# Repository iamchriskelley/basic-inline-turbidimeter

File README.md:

#Basic Inline Turbidimeter
##Purpose  
The Basic Inline Turbidimeter is designed to measure turbidity in a body of water, automatically, for the lowest possible price.  

##Function  
_How does the device measure a parameter?_  
This device is a back-scatter [nephelometrer](https://en.wikipedia.org/wiki/Nephelometer). A pair of infrared light-emitting diodes (IR LED) are mounted on either side of a light-to-frequency sensor. Some portion of this emitted light is scattered by suspended sediment as it passes through a sample of water. This scattered light is detected by an IR-sensitive [photodiode](https://en.wikipedia.org/wiki/Photodiode) mounted at a right angle to the center of the IR LED's light beam. The intensity of light detected by the photodiode is referenced to a calibration curve stored in the device's memory to interpolate the corresponding turbidity value, measured in [nephelometric turbidity units (NTU)](http://or.water.usgs.gov/grapher/fnu.html).  

_How does the device record data?_  
This device contains an SD card slot for storing data.   

_How does the device display data?_  
This device is intended for standalone data logging and does not include a display.  

_What units does the device report in?_  
Like all AWQUA turbidimeters, this device reports readings in  [nephelometric turbidity units (NTU)](http://or.water.usgs.gov/grapher/fnu.html).  

_How does the device communicate data electronically?_  
This device does not possess data telemetry capabilities, however they may be added for additional cost. See the [Communications](https://github.com/AWQUA/Communication) repo for options. 

##Use Case  
_Where can the device be safely used?_  
This device can handle temperatures up to 70C, and is intended for field conditions. It is water proof to at least one foot.

##Power  
_How is the device powered?_  
This device uses 3.3V DC power, and requires less than 100mA of current, and uses an internal 3.7V lithium polymer battery.

_How much power does it use?_  
In automated testing, this device was capable of taking a measurement every 15 minutes for 29.5 days.

##Standard and Testing  
_How was the device tested?_  
This device has so far only been tested in the Open Source Water lab. The testing consisted of:
(1) immersing a prototype device in a water bath which contains a spin plate for bath mixing  
(2) adding small doses of a colloidal suspension to the water bath while relaying readings from the prototype via Bluetooth  every 10 seconds
(3) on every fourth dose of colloidal suspension, sampling the water bath with a commercial handheld turbidimeter  
(4) analyzing the fit between the commercial and prototype open-source turbidimeter

_How did it perform?_  
Test results may be found in the `testing` subdirectory in the file `basic-inline-turbidimeter_analysis.20151021.xlsx`. These data will be updated as further testing is conducted.

_What performance standards does the device meet?_  
We have not evaluated this device against existing standards for backscatter turbidimeters yet, nor have we yet developed a new standard.

##Construction  

###Bill of Materials
| Quantity  | Part Description | Example Price (each) |
| :-------------: | ------------- | :-------------: |
| 1 | ATMega328P-PU microprocessor  | [$2.90](http://www.electrodragon.com/product/atmega328-with-arduino-optiboot-uno/)|
| 1 | LMT86 temperature sensor  | [$1.00](http://www.mouser.com/ProductDetail/Texas-Instruments/LMT86LP/?qs=sGAEpiMZZMvfFCidbTccA1jyVRrxk5nB%252bTEjPRynSGM%3d)|
| 1 | TSL230BRD  | [$5.03](http://www.mouser.com/ProductDetail/ams/TSL230BRD-TR/?qs=sGAEpiMZZMu97qiQi8P%252buifvOPr%252b402N67DKHn09PFo%3d)|
| 1 | LP2985 3.3V Voltage regulator  | [$1.04](http://www.mouser.com/ProductDetail/Texas-Instruments/LP2985-33DBVT/?qs=paYhMW8qfivCywxvLCGbYQ%3D%3D)|
| 2 | 10uF aluminum electrolytic capacitors  | [$0.24](http://www.mouser.com/ProductDetail/Nichicon/ULD1J100MDD1TD/?qs=sGAEpiMZZMvwFf0viD3Y3c1N%2fF%2fpDmX12XlNW9X9Y3vZmYyMo5GpOw%3d%3d)|
| 2 | 22pF ceramic capacitors  | [$0.03](http://www.mouser.com/ProductDetail/Vishay-BC-Components/K220J10C0GF5UH5/?qs=sGAEpiMZZMsh%252b1woXyUXj9nJp%252b8gphztXIKBUu3gv%252bs%3d)|
| 5 | 100nF ceramic capacitors  | [$0.06](http://www.mouser.com/ProductDetail/Vishay-BC-Components/K104Z15Y5VE5TL2/?qs=sGAEpiMZZMsh%252b1woXyUXj5VNmf0jXPWIrWjnp1zAXac%3d)|
| 4 | 100 ohm resistors  | [$0.10](http://www.mouser.com/ProductDetail/KOA-Speer/MOS1-2CT52R101J/?qs=sGAEpiMZZMtlubZbdhIBICYVxaT5CDYBpEIIN%2f0BoAk%3d)|
| 1 | 220 ohm resistors  | [$0.10](http://www.mouser.com/ProductDetail/KOA-Speer/MOS1-2CT52R221J/?qs=sGAEpiMZZMtlubZbdhIBICYVxaT5CDYBStqm8FrIljg%3d)|
| 1 | 1K ohm resistors 1% tolerance | [$0.10](http://www.mouser.com/ProductDetail/Vishay-Beyschlag/MBB02070C1001FCT00/?qs=sGAEpiMZZMtlubZbdhIBIAA6NYEPHyksoxlYyK2s%252btM%3d)|
| 4 | 10K ohm resistors  | [$0.10](http://www.mouser.com/ProductDetail/Vishay-Beyschlag/MBA02040C1002FCT00/?qs=sGAEpiMZZMtlubZbdhIBIP7908E9uONJr6Tgqqo7oLA%3d)|
| 1 | IR LED  | [$0.47](http://www.mouser.com/ProductDetail/Kingbright/WP7113SF4C/?qs=sGAEpiMZZMvAL21a%2fDhxMro1KOf4QOs%252bCw5JRgjZK8o%3d)|
| 1 | Momentary contact button  | [$1.50](http://www.mouser.com/)|
| 1 | SPST power switch  | [$1.50](http://www.mouser.com/)|
| x | Header pins (0.1" spacing)  | [$1.50](http://www.mouser.com/)|
|||
||Total Cost:|$xx.xx|
###Circuit Board
####Schematic

####Layout

###Assembly
[forthcoming]  
##FAQ and Troubleshooting  
###Online Resources

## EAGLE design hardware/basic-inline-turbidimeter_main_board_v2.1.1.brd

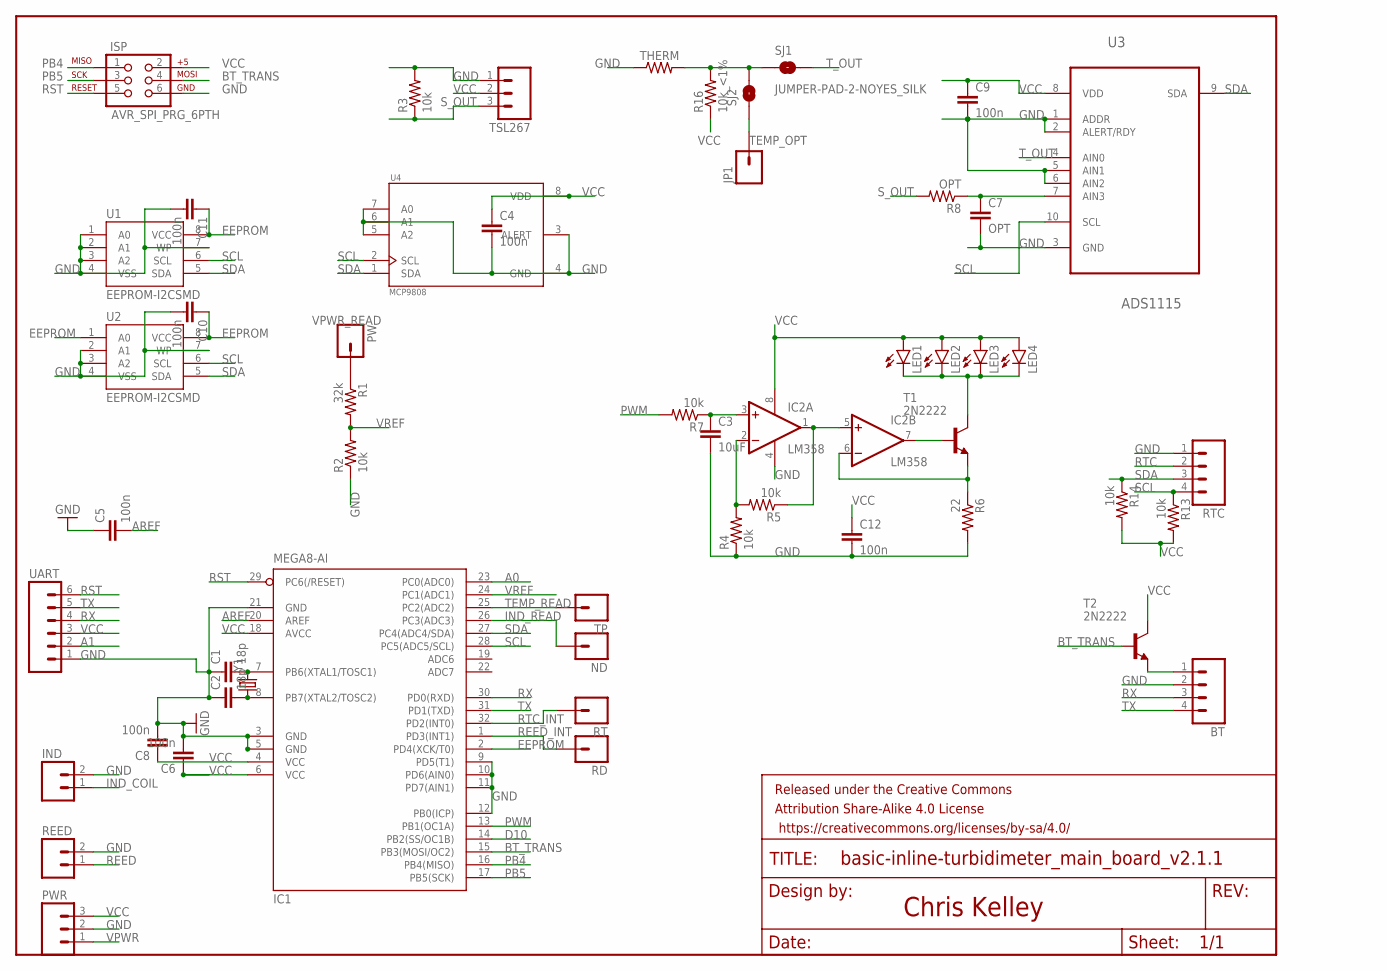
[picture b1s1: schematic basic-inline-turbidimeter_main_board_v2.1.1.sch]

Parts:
BT: M04PTH; 1X04
C1, C2: 18p; 0603-CAP
C3: 10uF; 0603-CAP
C4, C5, C6, C8, C9, C10, C11, C12: 100n; 0603-CAP
C7: OPT; 0603-CAP
FRAME1: FRAME-LETTER; CREATIVE_COMMONS
IC1: MEGA8-AI; TQFP32-08
IC2: LM358; SO08
IND: M02PTH; 1X02
ISP: AVR_SPI_PRG_6PTH; 2X3
JP1: M01PTH; 1X01
LED1, LED2, LED3, LED4: LED5MM
ND: M01PTH; 1X01
PW: M01PTH; 1X01
PWR: M03PTH; 1X03
R1: 32k; 0603-RES
R2, R3, R4, R5, R7, R13, R14: 10k; 0603-RES
R6: 22; 0603-RES
R8: OPT; 0603-RES
R16: 10k_<1%; 0603-RES
RD: M01PTH; 1X01
REED: M02PTH; 1X02
RT: M01PTH; 1X01
RTC: M04PTH; 1X04
SJ1, SJ2: JUMPER-PAD-2-NOYES_SILK; PAD-JUMPER-2-NO_YES_SILK
T1, T2: 2N2222; TO92-EBC-OVAL
THERM: RESISTOR0603-RES; 0603-RES
TP: M01PTH; 1X01
TSL267: M03PTH; 1X03
U1, U2: EEPROM-I2CSMD; SO08
U3: ADS1115; SOP50P490X110-10N
U4: MCP9808; SOP65P490X110-8N
UART: M06SILK_FEMALE_PTH; 1X06
Y1: CRYSTAL5X3; CRYSTAL-SMD-5X3

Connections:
A0: IC1.23 (PC0(ADC0))
A1: UART.2
AREF: C5.2, IC1.20 (AREF)
BT_TRANS: IC1.15 (PB3(MOSI/OC2)), ISP.4, T2.B
D10: IC1.14 (PB2(SS/OC1B))
EEPROM: C10.1, C11.1, IC1.2 (PD4(XCK/T0)), U1.8 (VCC), U2.1 (A0), U2.8 (VCC)
GND: BT.2, C1.1, C2.1, C3.2, C4.2, C5.1, C6.2, C7.2, C8.2, C9.2, C10.2, C11.2, C12.2, IC1.3 (GND), IC1.5 (GND), IC1.9 (PD5(T1)), IC1.10 (PD6(AIN0)), IC1.11 (PD7(AIN1)), IC1.12 (PB0(ICP)), IC1.21 (GND), IC2.4 (V-), IND.2, ISP.6, PWR.2, R2.1, R3.2, R4.1, R6.2, REED.2, RTC.1, THERM.1, TSL267.1, U1.1 (A0), U1.2 (A1), U1.3 (A2), U1.4 (VSS), U1.7 (WP), U2.2 (A1), U2.3 (A2), U2.4 (VSS), U2.7 (WP), U3.1 (ADDR), U3.2 (ALERT/RDY), U3.3 (GND), U3.5 (AIN1), U3.6 (AIN2), U4.3 (ALERT), U4.4 (GND), U4.5 (A2), U4.6 (A1), U4.7 (A0), UART.1
IND_COIL: IND.1
IND_READ: IC1.26 (PC3(ADC3)), ND.1
unnamed: LED1.K (C), LED2.K (C), LED3.K (C), LED4.K (C), T1.C
unnamed: C7.1, R8.1, U3.7 (AIN3)
unnamed: C3.1, IC2.3 (+IN), R7.1
unnamed: IC2.1 (OUT), IC2.5 (+IN), R5.1
unnamed: IC2.7 (OUT), T1.B
unnamed: IC2.2 (-IN), R4.2, R5.2
unnamed: IC2.6 (-IN), R6.1, T1.E
unnamed: BT.1, T2.E
unnamed: R16.2, SJ1.1, SJ2.2, THERM.2
PB4: IC1.16 (PB4(MISO)), ISP.1
PB5: IC1.17 (PB5(SCK)), ISP.3
PWM: IC1.13 (PB1(OC1A)), R7.2
Q1: C2.2, IC1.8 (PB7(XTAL2/TOSC2)), Y1.1
Q2: C1.2, IC1.7 (PB6(XTAL1/TOSC1)), Y1.3 (2)
REED: REED.1
REED_INT: IC1.1 (PD3(INT1)), RD.1
RST: IC1.29 (PC6(/RESET)), ISP.5, UART.6
RTC: RTC.2
RTC_INT: IC1.32 (PD2(INT0)), RT.1
RX: BT.3, IC1.30 (PD0(RXD)), UART.4
SCL: IC1.28 (PC5(ADC5/SCL)), R13.1, RTC.4, U1.6 (SCL), U2.6 (SCL), U3.10 (SCL), U4.2 (SCL)
SDA: IC1.27 (PC4(ADC4/SDA)), R14.1, RTC.3, U1.5 (SDA), U2.5 (SDA), U3.9 (SDA), U4.1 (SDA)
S_OUT: R3.1, R8.2, TSL267.3
TEMP_OPT: JP1.1, SJ2.1
TEMP_READ: IC1.25 (PC2(ADC2)), TP.1
TX: BT.4, IC1.31 (PD1(TXD)), UART.5
T_OUT: SJ1.2, U3.4 (AIN0)
VCC: C4.1, C6.1, C8.1, C9.1, C12.1, IC1.4 (VCC), IC1.6 (VCC), IC1.18 (AVCC), IC2.8 (V+), ISP.2, LED1.A, LED2.A, LED3.A, LED4.A, PWR.3, R13.2, R14.2, R16.1, T2.C, TSL267.2, U3.8 (VDD), U4.8 (VDD), UART.3
VPWR: PWR.1
VPWR_READ: PW.1, R1.1
VREF: IC1.24 (PC1(ADC1)), R1.2, R2.2

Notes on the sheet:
Chris Kelley

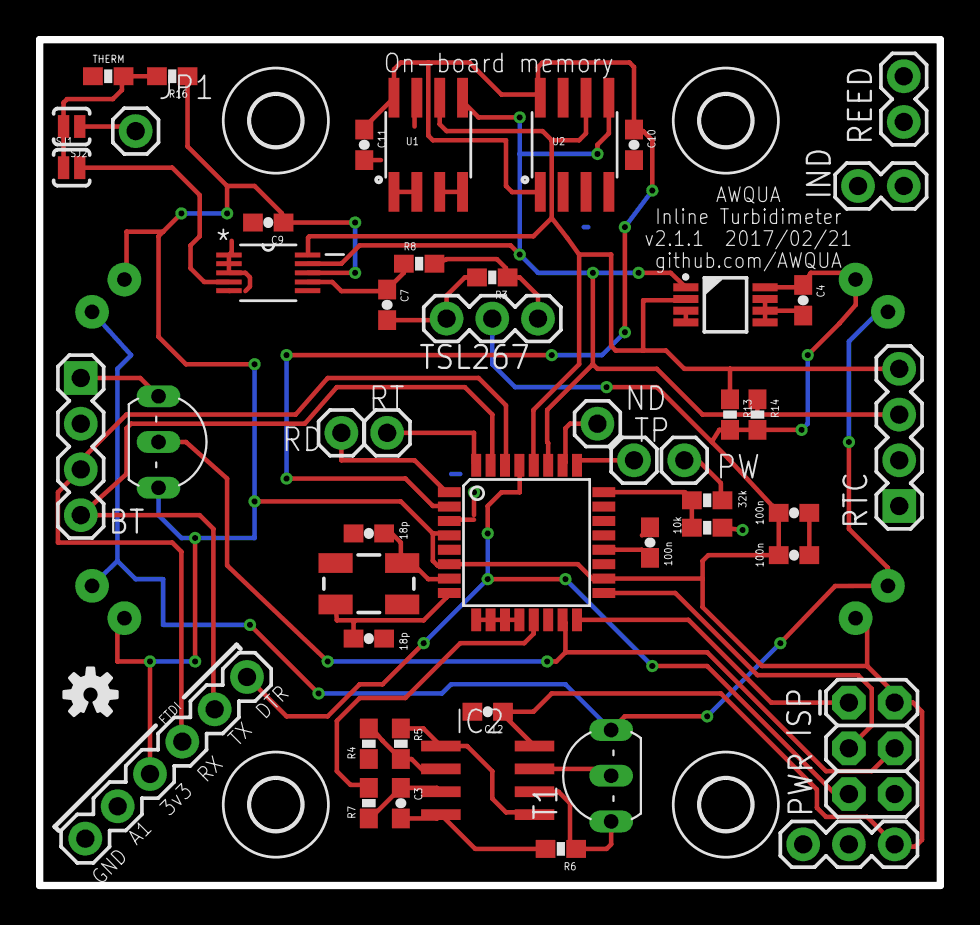
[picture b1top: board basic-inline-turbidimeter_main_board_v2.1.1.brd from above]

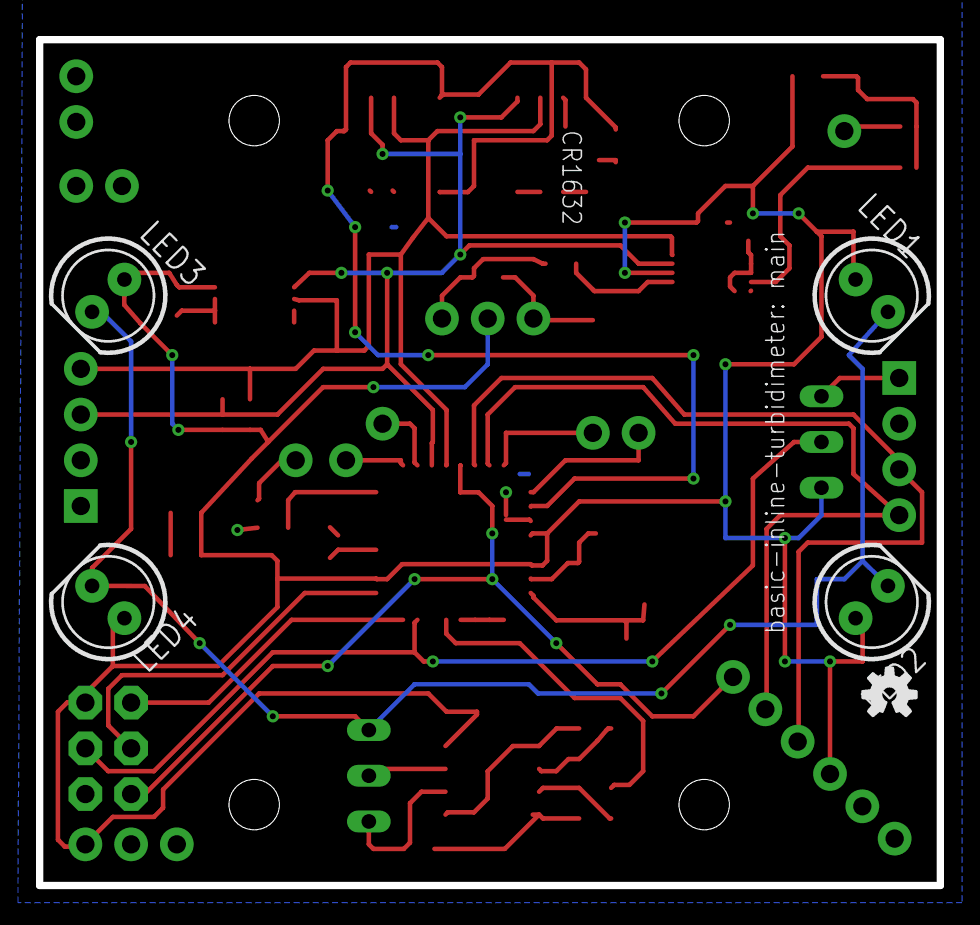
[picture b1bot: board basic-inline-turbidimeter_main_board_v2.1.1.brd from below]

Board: 2 copper layers, 50.0 x 47.0 mm, 60 parts (5 on the bottom side), 33 nets.

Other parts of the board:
U$1, U$3, U$5, U$6: 2,8
U$2, U$8: OSHW-LOGO-S

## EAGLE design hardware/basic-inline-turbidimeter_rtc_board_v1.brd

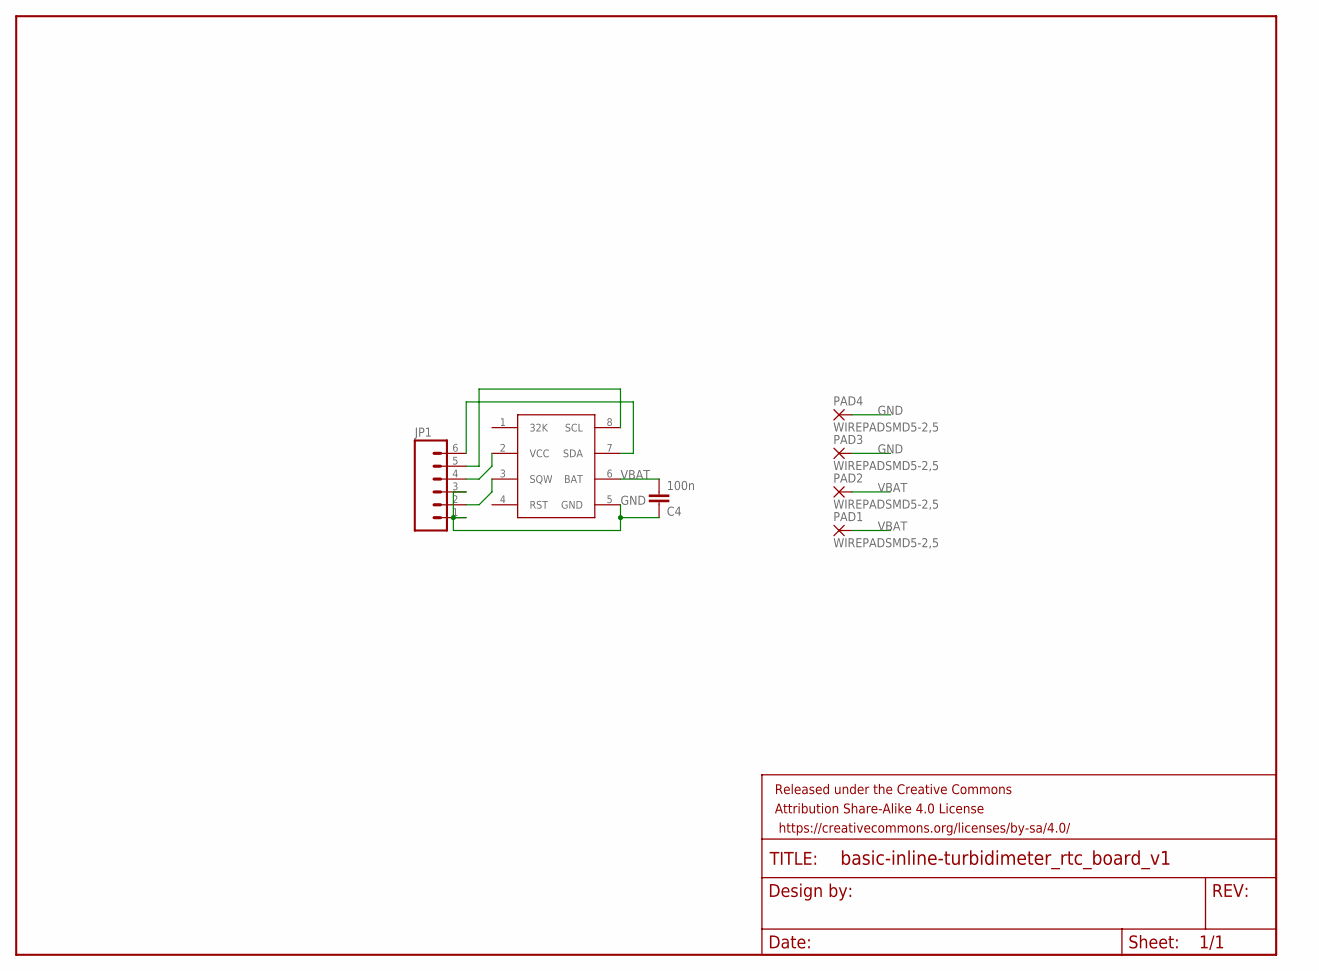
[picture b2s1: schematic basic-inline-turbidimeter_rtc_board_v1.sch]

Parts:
*RTC: DS3231M
C4: 100n; 0603-CAP
FRAME1: FRAME-LETTER; CREATIVE_COMMONS
JP1: M06SILK_FEMALE_PTH; 1X06
PAD1, PAD2, PAD3, PAD4: WIREPADSMD5-2,5; 5-2,5

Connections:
GND: *RTC.5 (GND), C4.1, JP1.1, JP1.3, PAD3.1, PAD4.1
unnamed: *RTC.3 (SQW), JP1.2
SCL: *RTC.8 (SCL), JP1.5
SDA: *RTC.7 (SDA), JP1.6
VBAT: *RTC.6 (BAT), C4.2, PAD1.1, PAD2.1
VCC: *RTC.2 (VCC), JP1.4

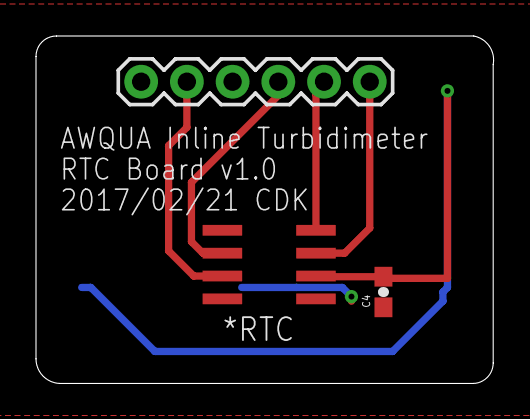
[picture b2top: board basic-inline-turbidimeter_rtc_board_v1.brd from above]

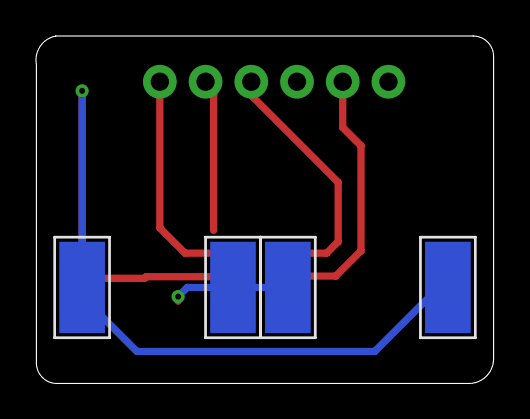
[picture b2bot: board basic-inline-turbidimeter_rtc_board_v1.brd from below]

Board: 2 copper layers, 25.4 x 19.3 mm, 8 parts (4 on the bottom side), 6 nets.

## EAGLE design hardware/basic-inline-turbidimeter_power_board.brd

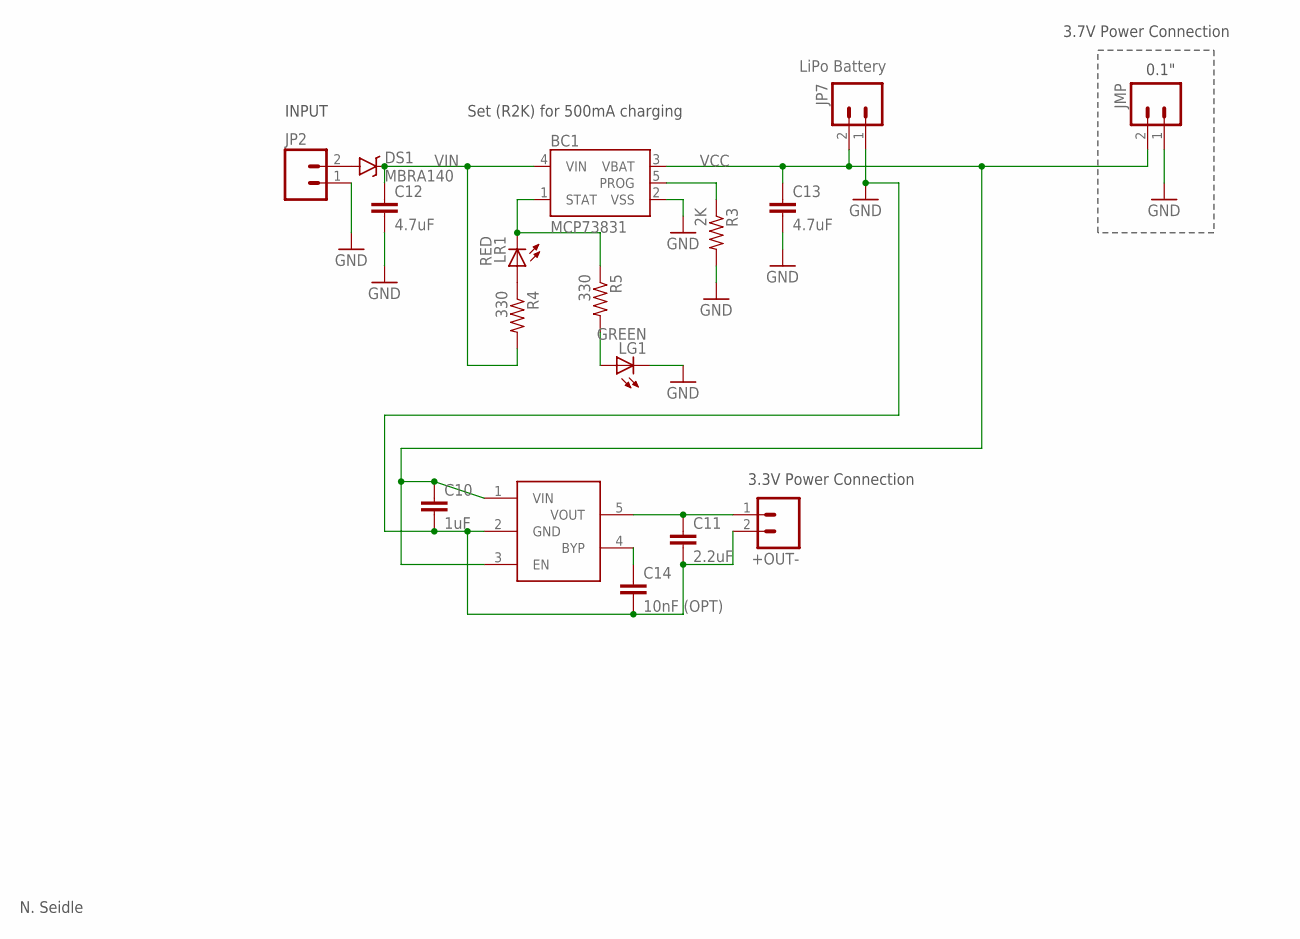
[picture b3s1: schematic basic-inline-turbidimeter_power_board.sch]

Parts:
+OUT-: M02PTH; 1X02
BC1: MCP73831; SOT23-5
C10: 1uF; 0603-CAP
C11: 2.2uF; 0603-CAP
C12, C13: 4.7uF; 0402-CAP
C14: 10nF (OPT); 0603-CAP
DS1: MBRA140; SMA-DIODE
JMP: M02PTH; 1X02
JP2: M02PTH; 1X02
JP7: LiPo Battery; JST-2-SMD
LG1: GREEN; LED-0603
LR1: RED; LED-0603
R3: 2K; 0402-RES
R4, R5: 330; 0402-RES
VR1: LP2985

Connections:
GND: +OUT-.2, BC1.2 (VSS), C10.2, C11.2, C12.2, C13.2, C14.2, JMP.1, JP2.1, JP7.1, LG1.C, R3.2, VR1.2 (GND)
unnamed: C14.1, VR1.4 (BYP)
unnamed: LG1.A, R5.2
unnamed: LR1.A, R4.1
unnamed: +OUT-.1, C11.1, VR1.5 (VOUT)
unnamed: DS1.A, JP2.2
PROG: BC1.5 (PROG), R3.1
STAT: BC1.1 (STAT), LR1.C, R5.1
VCC: BC1.3 (VBAT), C10.1, C13.1, JMP.2, JP7.2, VR1.1 (VIN), VR1.3 (EN)
VIN: BC1.4 (VIN), C12.1, DS1.C, R4.2

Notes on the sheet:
3.7V Power Connection
0.1"
N. Seidle
3.3V Power Connection
Set (R2K) for 500mA charging
INPUT

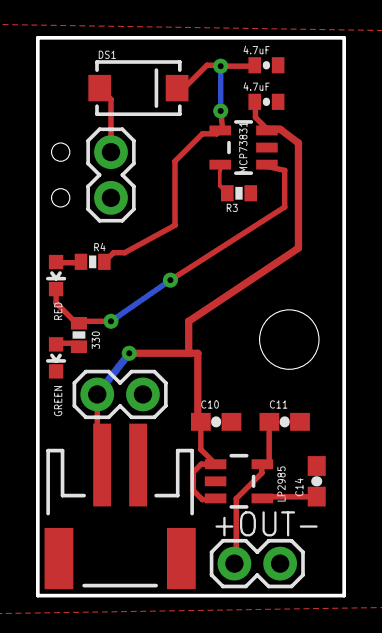
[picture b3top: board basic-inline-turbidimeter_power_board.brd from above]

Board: 2 copper layers, 17.0 x 31.0 mm, 18 parts (0 on the bottom side), 10 nets.

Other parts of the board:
JP1: STAND-OFF

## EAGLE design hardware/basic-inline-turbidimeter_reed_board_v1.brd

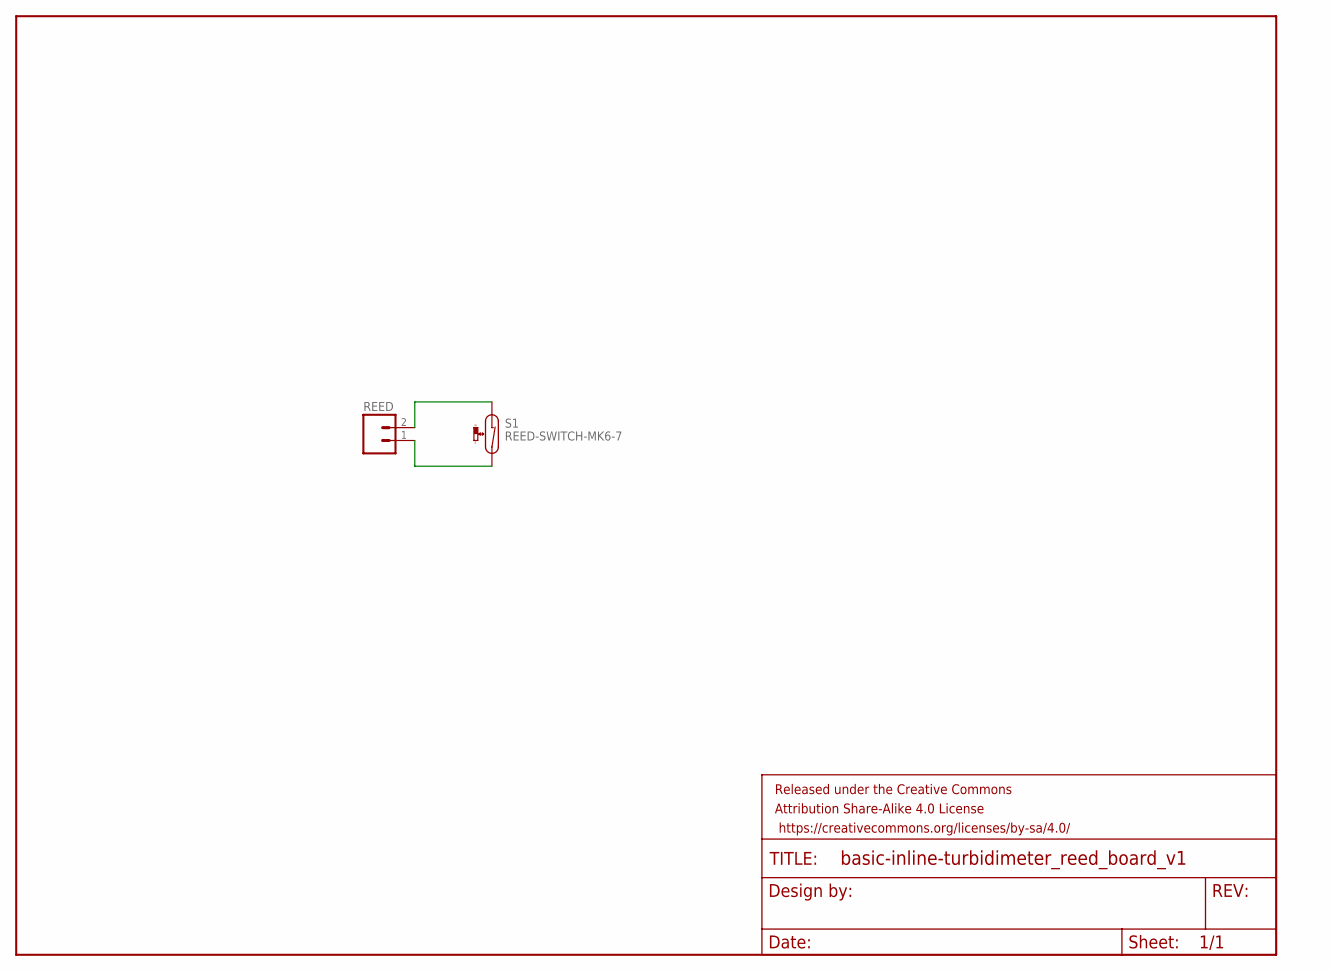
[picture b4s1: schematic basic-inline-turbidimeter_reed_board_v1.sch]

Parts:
FRAME1: FRAME-LETTER; CREATIVE_COMMONS
REED: M02PTH; 1X02
S1: REED-SWITCH-MK6-7; MK6-7

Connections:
unnamed: REED.2, S1.1
unnamed: REED.1, S1.2

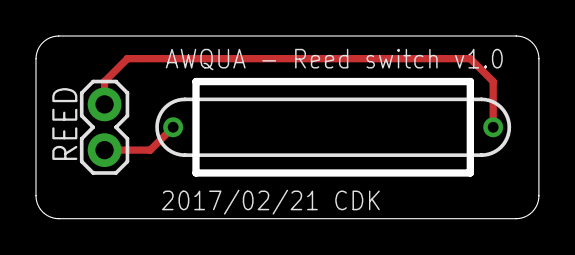
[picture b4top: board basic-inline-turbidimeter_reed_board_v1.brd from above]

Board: 2 copper layers, 27.9 x 10.2 mm, 3 parts (0 on the bottom side), 2 nets.

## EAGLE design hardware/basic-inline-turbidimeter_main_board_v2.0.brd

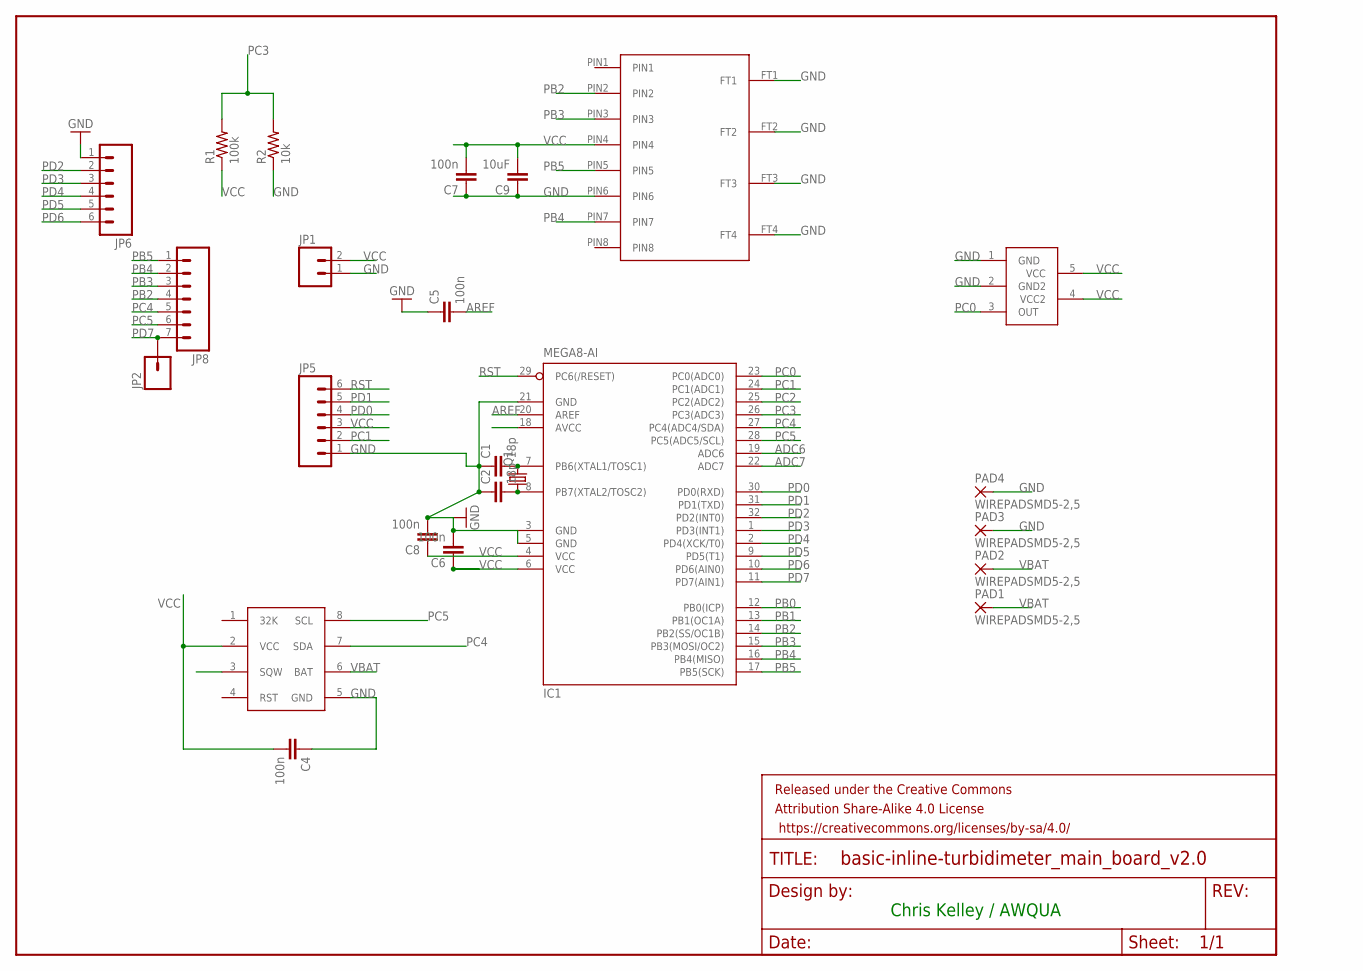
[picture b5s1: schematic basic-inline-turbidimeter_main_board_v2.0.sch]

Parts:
*RTC: DS3231M
C1, C2: 18p; 0603-CAP
C4, C5, C6, C7, C8: 100n; 0603-CAP
C9: 10uF; 0603-CAP
FRAME1: FRAME-LETTER; CREATIVE_COMMONS
IC1: MEGA8-AI; TQFP32-08
JP1: M02PTH; 1X02
JP2: M01PTH; 1X01
JP5, JP6: M06SILK_FEMALE_PTH; 1X06
JP8: M07; 1X07
MICRO-SD: MICROSD-1010030368
PAD1, PAD2, PAD3, PAD4: WIREPADSMD5-2,5; 5-2,5
Q1: CRYSTAL5X3; CRYSTAL-SMD-5X3
R1: 100k; 0603-RES
R2: 10k; 0603-RES
T1: LMT86

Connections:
ADC6: IC1.19 (ADC6)
ADC7: IC1.22 (ADC7)
AREF: C5.2, IC1.20 (AREF)
GND: *RTC.5 (GND), C1.1, C2.1, C4.1, C5.1, C6.2, C7.1, C8.2, C9.1, IC1.3 (GND), IC1.5 (GND), IC1.21 (GND), JP1.1, JP5.1, JP6.1, MICRO-SD.FT1, MICRO-SD.FT2, MICRO-SD.FT3, MICRO-SD.FT4, MICRO-SD.PIN6, PAD3.1, PAD4.1, R2.1, T1.1 (GND), T1.2 (GND2)
PB0: IC1.12 (PB0(ICP))
PB1: IC1.13 (PB1(OC1A))
PB2: IC1.14 (PB2(SS/OC1B)), JP8.4, MICRO-SD.PIN2
PB3: IC1.15 (PB3(MOSI/OC2)), JP8.3, MICRO-SD.PIN3
PB4: IC1.16 (PB4(MISO)), JP8.2, MICRO-SD.PIN7
PB5: IC1.17 (PB5(SCK)), JP8.1, MICRO-SD.PIN5
PC0: IC1.23 (PC0(ADC0)), T1.3 (OUT)
PC1: IC1.24 (PC1(ADC1)), JP5.2
PC2: IC1.25 (PC2(ADC2))
PC3: IC1.26 (PC3(ADC3)), R1.2, R2.2
PC4: *RTC.7 (SDA), IC1.27 (PC4(ADC4/SDA)), JP8.5
PC5: *RTC.8 (SCL), IC1.28 (PC5(ADC5/SCL)), JP8.6
PD0: IC1.30 (PD0(RXD)), JP5.4
PD1: IC1.31 (PD1(TXD)), JP5.5
PD2: IC1.32 (PD2(INT0)), JP6.2
PD3: IC1.1 (PD3(INT1)), JP6.3
PD4: IC1.2 (PD4(XCK/T0)), JP6.4
PD5: IC1.9 (PD5(T1)), JP6.5
PD6: IC1.10 (PD6(AIN0)), JP6.6
PD7: IC1.11 (PD7(AIN1)), JP2.1, JP8.7
Q1: C2.2, IC1.8 (PB7(XTAL2/TOSC2)), Q1.1
Q2: C1.2, IC1.7 (PB6(XTAL1/TOSC1)), Q1.3 (2)
RST: IC1.29 (PC6(/RESET)), JP5.6
VBAT: *RTC.6 (BAT), PAD1.1, PAD2.1
VCC: *RTC.2 (VCC), C4.2, C6.1, C7.2, C8.1, C9.2, IC1.4 (VCC), IC1.6 (VCC), IC1.18 (AVCC), JP1.2, JP5.3, MICRO-SD.PIN4, R1.1, T1.4 (VCC2), T1.5 (VCC)

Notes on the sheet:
Chris Kelley / AWQUA

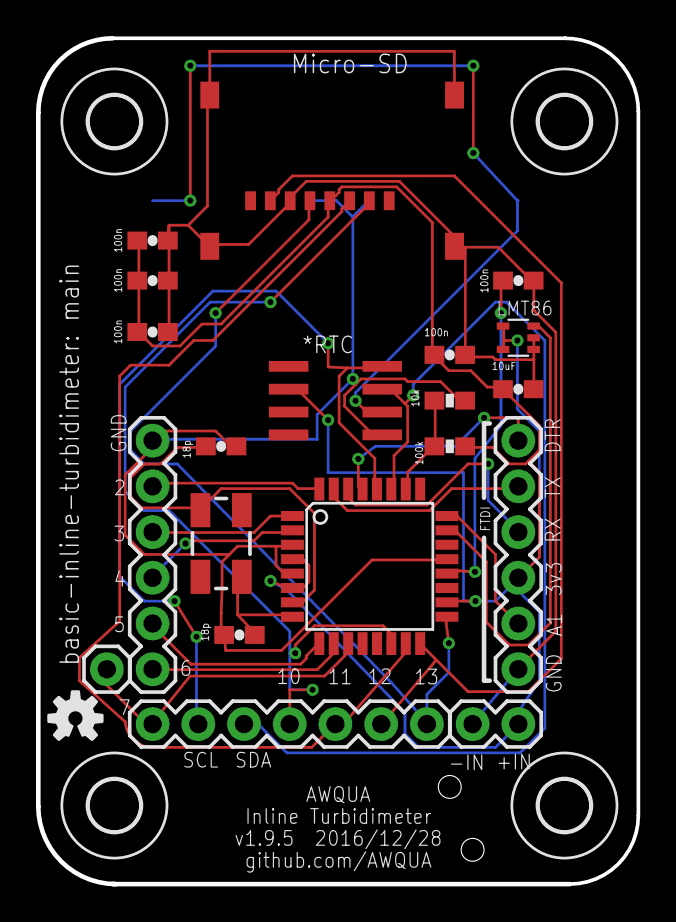
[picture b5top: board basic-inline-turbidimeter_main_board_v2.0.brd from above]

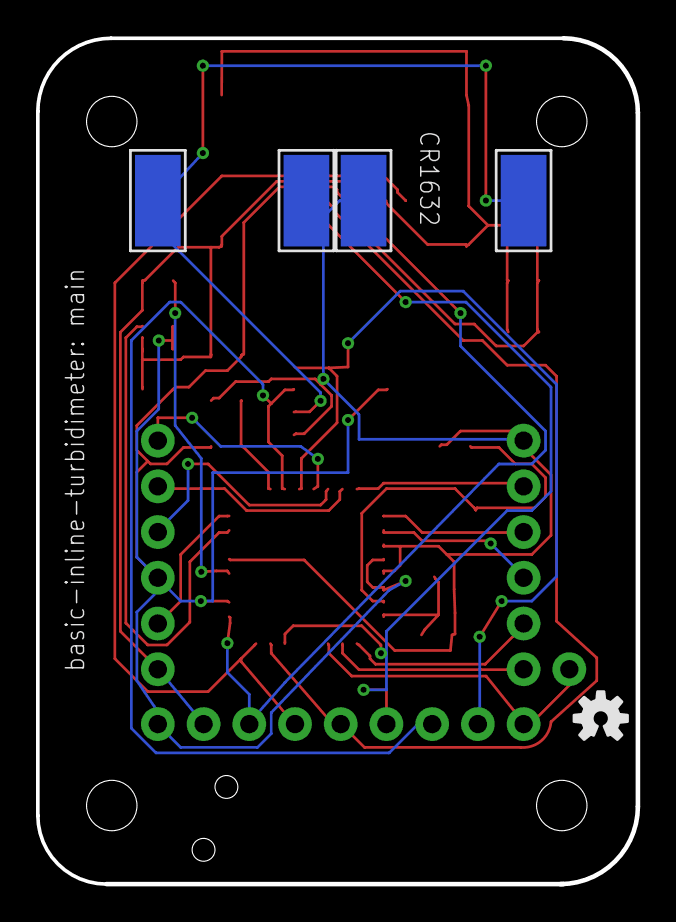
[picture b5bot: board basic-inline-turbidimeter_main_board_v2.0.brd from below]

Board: 2 copper layers, 33.3 x 47.0 mm, 31 parts (5 on the bottom side), 24 nets.

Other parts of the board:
U$1, U$3, U$5, U$6: 2,8
U$2, U$8: OSHW-LOGO-S

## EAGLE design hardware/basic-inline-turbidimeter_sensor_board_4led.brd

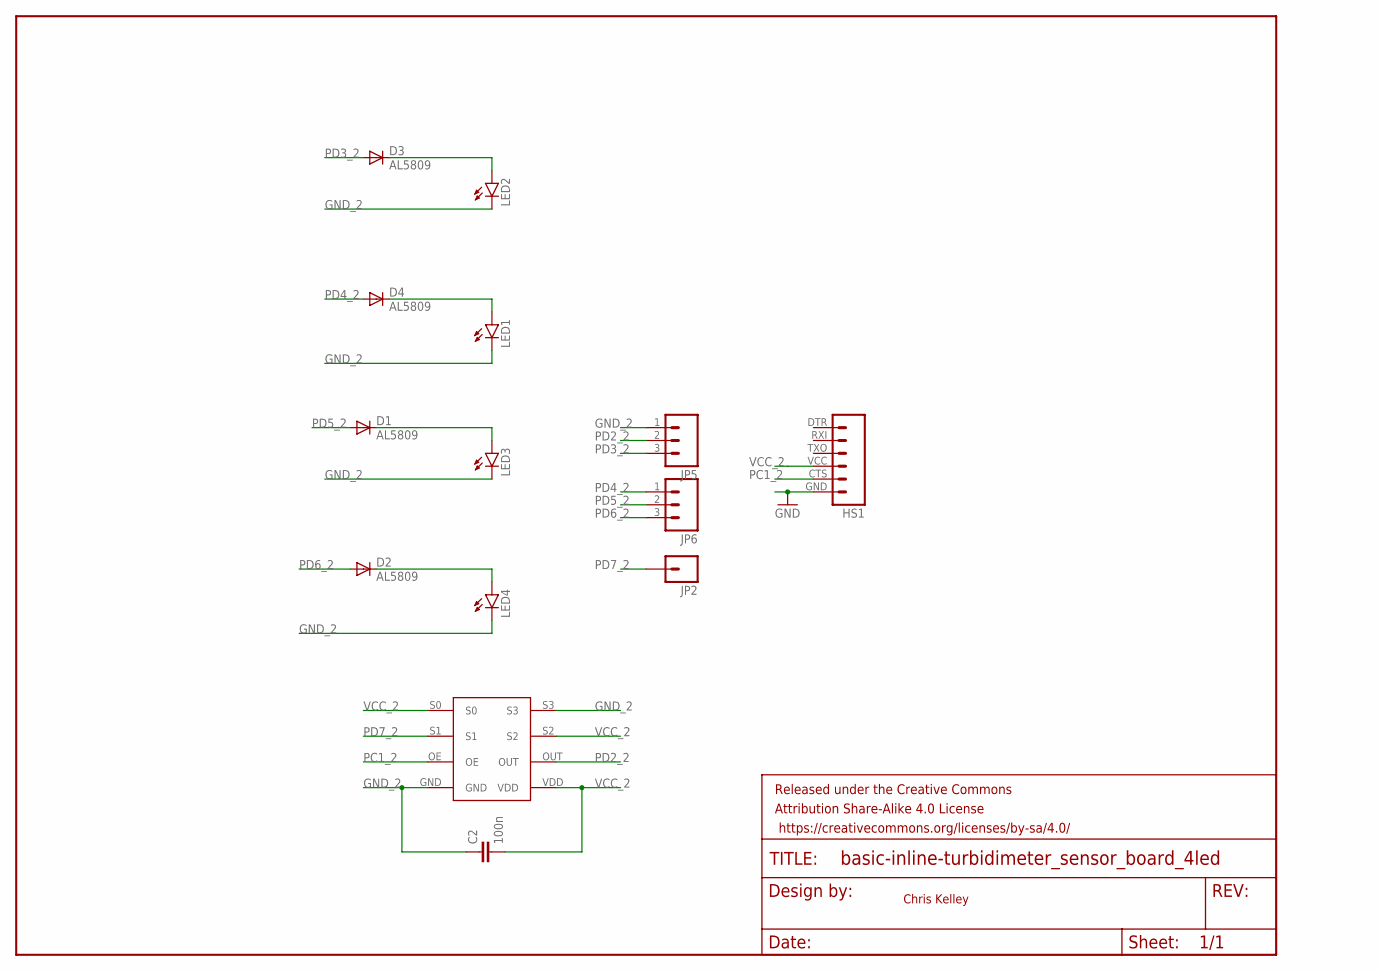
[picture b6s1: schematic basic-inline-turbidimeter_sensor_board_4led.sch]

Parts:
C2: 100n; 0805
D1, D2, D3, D4: AL5809; SOD123
FRAME1: FRAME-LETTER; CREATIVE_COMMONS
HS1: M06SIP; 1X06
JP2: M01PTH; 1X01
JP5, JP6: M03PTH; 1X03
LED1, LED2, LED3, LED4: LED5MM
S1: TSL230RDSMD; TSL230RD

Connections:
GND_2: C2.1, HS1.GND (6), JP5.1, LED1.K (C), LED2.K (C), LED3.K (C), LED4.K (C), S1.GND, S1.S3
LED1: D1.C, LED3.A
LED2: D2.C, LED4.A
unnamed: D4.C, LED1.A
unnamed: D3.C, LED2.A
PC1_2: HS1.CTS (5), S1.OE
PD2_2: JP5.2, S1.OUT
PD3_2: D3.A, JP5.3
PD4_2: D4.A, JP6.1
PD5_2: D1.A, JP6.2
PD6_2: D2.A, JP6.3
PD7_2: JP2.1, S1.S1
VCC_2: C2.2, HS1.VCC (4), S1.S0, S1.S2, S1.VDD

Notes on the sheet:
Chris Kelley

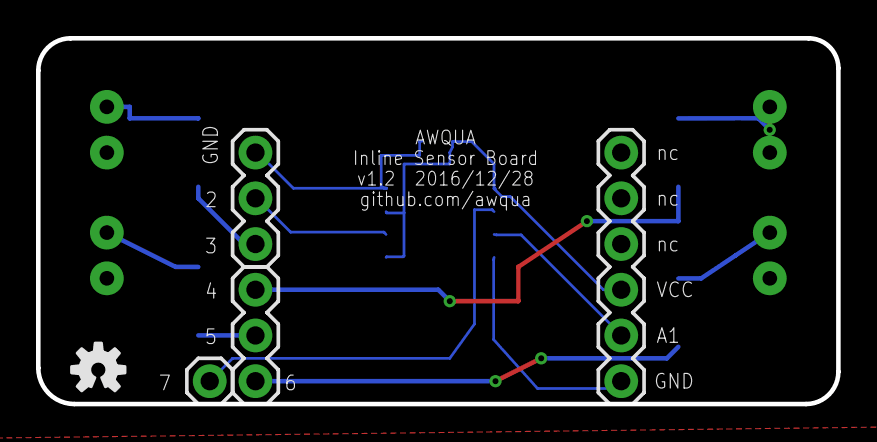
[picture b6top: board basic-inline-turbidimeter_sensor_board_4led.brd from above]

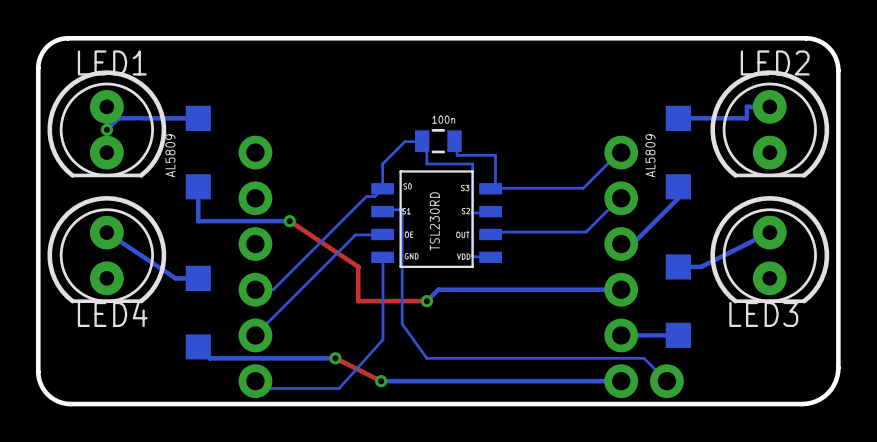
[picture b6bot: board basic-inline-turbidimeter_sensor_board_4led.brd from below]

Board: 2 copper layers, 44.5 x 20.3 mm, 16 parts (10 on the bottom side), 13 nets.

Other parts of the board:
U$5: OSHW-LOGO-S

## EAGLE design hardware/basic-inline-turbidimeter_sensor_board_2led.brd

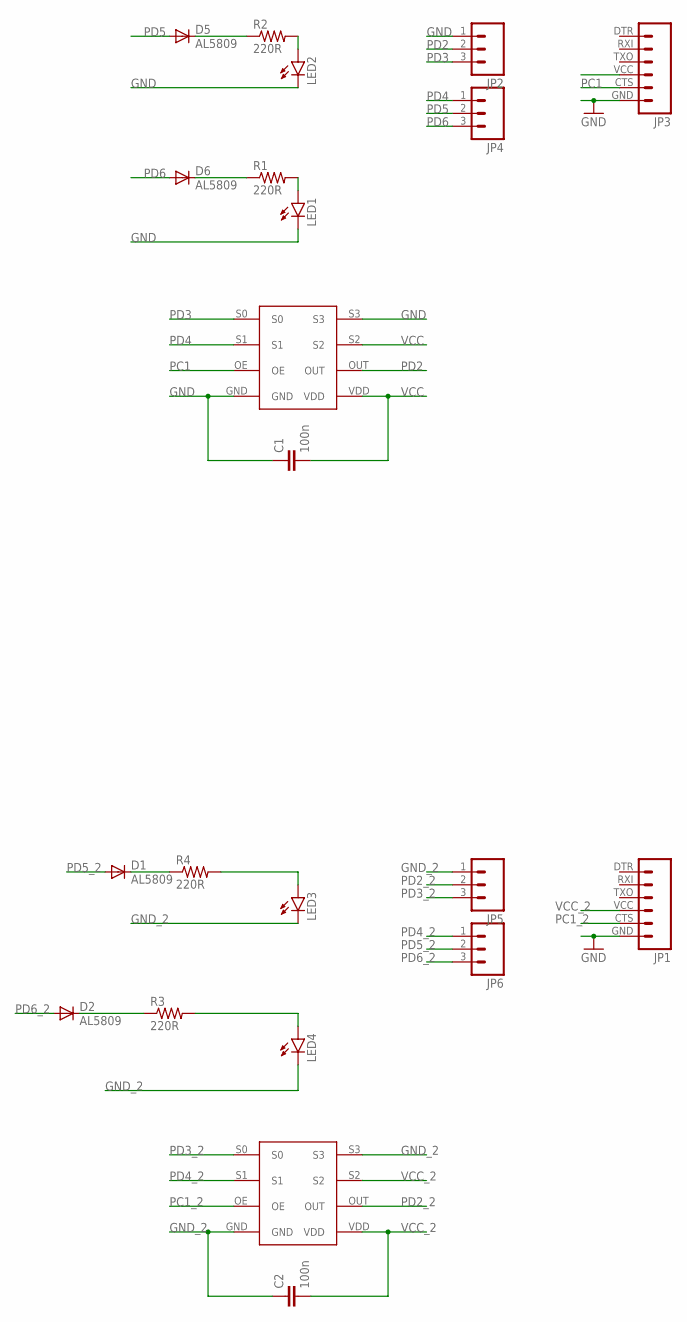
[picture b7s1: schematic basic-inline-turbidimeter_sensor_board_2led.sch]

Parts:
C1, C2: 100n; 0805
D1, D2, D5, D6: AL5809; SOD123
JP1, JP3: M06SIP; 1X06
JP2, JP4, JP5, JP6: M03PTH; 1X03
LED1, LED2, LED3, LED4: LED5MM
R1, R2, R3, R4: 220R; 0603-RES
U$1, U$3: TSL230RDSMD; TSL230RD

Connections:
GND: C1.1, JP2.1, JP3.GND (6), LED1.K (C), LED2.K (C), U$1.GND, U$1.S3
GND_2: C2.1, JP1.GND (6), JP5.1, LED3.K (C), LED4.K (C), U$3.GND, U$3.S3
LED1: D1.C, R4.1
LED2: D2.C, R3.1
unnamed: LED1.A, R1.2
unnamed: LED4.A, R3.2
unnamed: LED2.A, R2.2
unnamed: LED3.A, R4.2
unnamed: D6.C, R1.1
unnamed: D5.C, R2.1
PC1: JP3.CTS (5), U$1.OE
PC1_2: JP1.CTS (5), U$3.OE
PD2: JP2.2, U$1.OUT
PD2_2: JP5.2, U$3.OUT
PD3: JP2.3, U$1.S0
PD3_2: JP5.3, U$3.S0
PD4: JP4.1, U$1.S1
PD4_2: JP6.1, U$3.S1
PD5: D5.A, JP4.2
PD5_2: D1.A, JP6.2
PD6: D6.A, JP4.3
PD6_2: D2.A, JP6.3
VCC: C1.2, JP3.VCC (4), U$1.S2, U$1.VDD
VCC_2: C2.2, JP1.VCC (4), U$3.S2, U$3.VDD

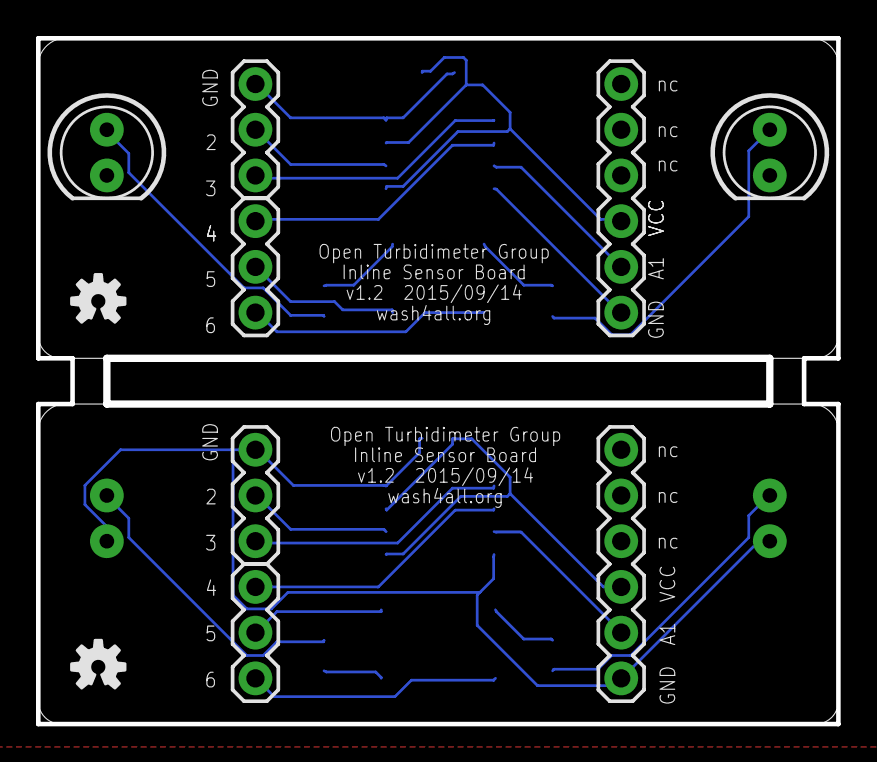
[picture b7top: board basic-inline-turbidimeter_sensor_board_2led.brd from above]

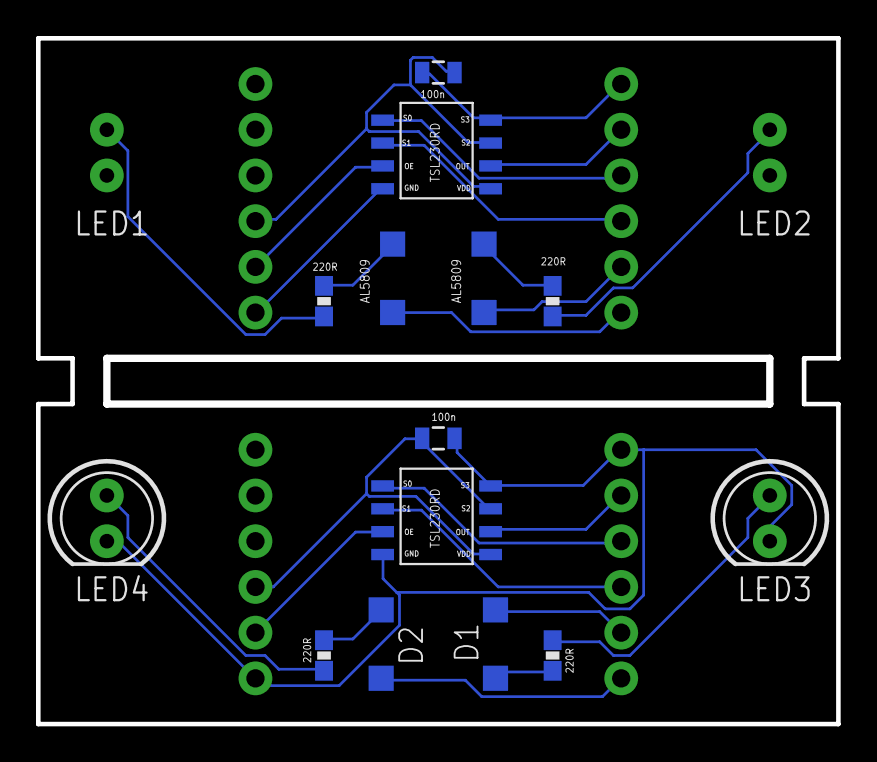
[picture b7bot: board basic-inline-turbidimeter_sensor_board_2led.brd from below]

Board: 2 copper layers, 44.5 x 38.1 mm, 24 parts (14 on the bottom side), 24 nets.

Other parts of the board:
U$2, U$5: OSHW-LOGO-S

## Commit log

2016-03-27 migrating from AWQUA/Measurement until polished
2017-01-16 hardware updates
2017-03-12 minor updates
2017-03-17 adding solder paste mask for v2.1
2017-03-28 added svg fror acrylic window laser cutting

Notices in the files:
parts and their libraries:
SparkFun-Connectors: Licensing: CC v3.0 Share-Alike You are welcome to use this library for commercial purposes.
SparkFun-Aesthetics: Licensing: Creative Commons ShareAlike 4.0 International - https://creativecommons.org/licenses/by-sa/4.0
SparkFun-Aesthetics: Released under the Creative Commons
